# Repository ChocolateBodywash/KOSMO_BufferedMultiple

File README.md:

## KOSMO Format Buffered Multiple

A KOSMO format of a dead simple Buffered Multiple circuit. This one is 25cm, perfect for smaller setups

---
Note: This was created by a hobbyist with no formal engineering training outside various late night YouTube binges. 
I’ve confirmed these designs to work but I make no guarantees on the design working efficiently.. or working at all.

Additional credit: Analog Output (Richard Holmes) for footprint libraries and front panel templates.

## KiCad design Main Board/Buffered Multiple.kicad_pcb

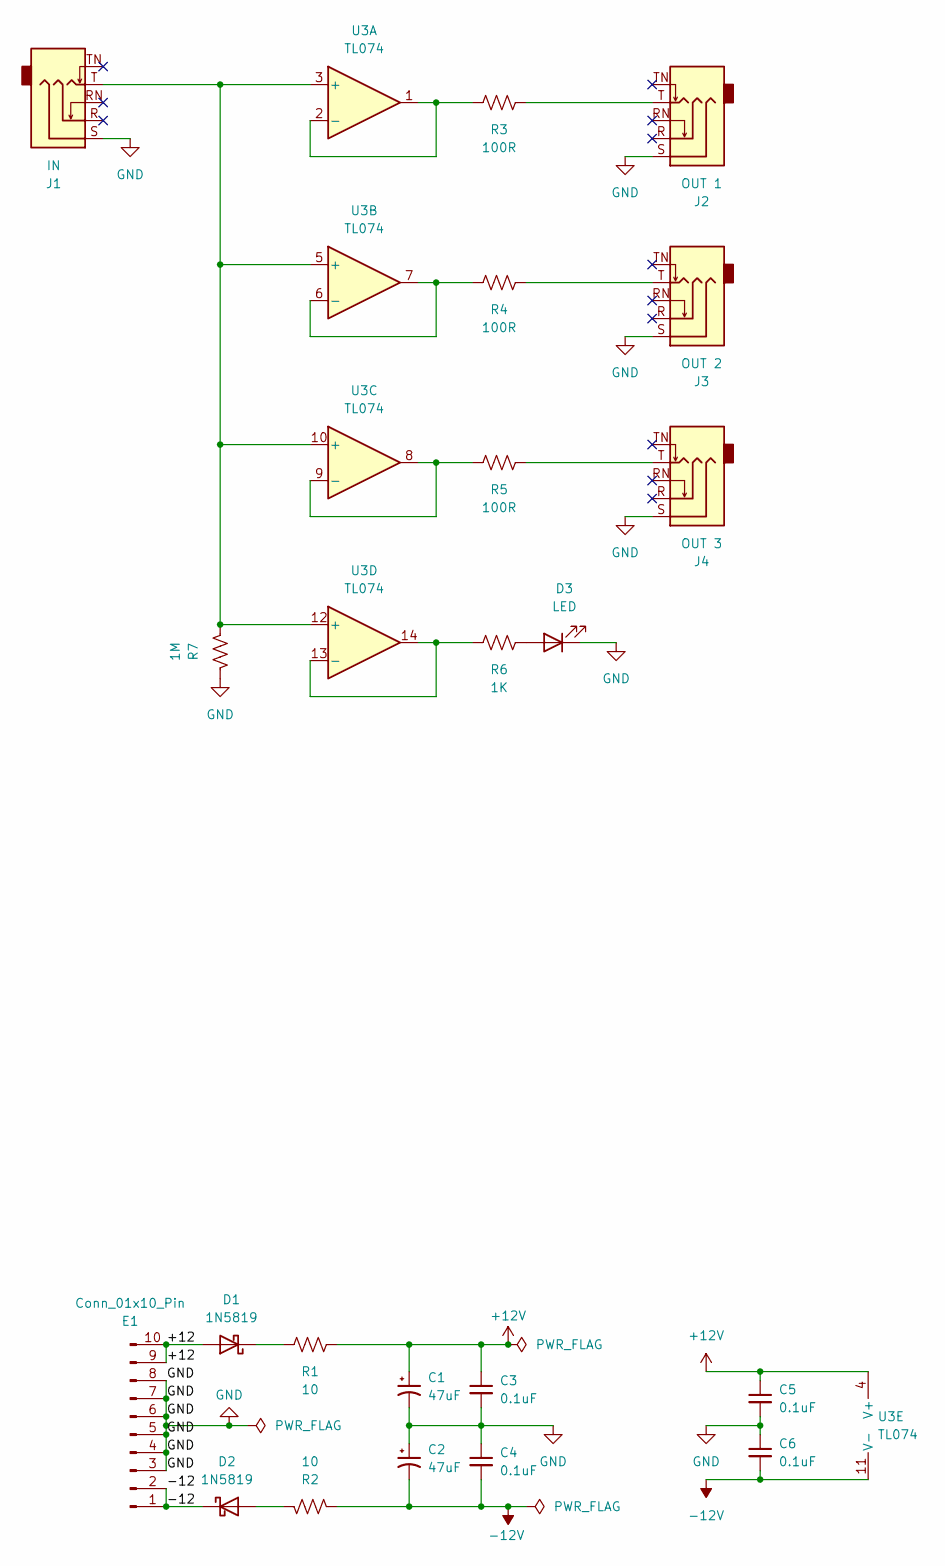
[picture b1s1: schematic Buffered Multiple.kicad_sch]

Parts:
C1, C2: 47uF; CP_Radial_D5.0mm_P2.50mm
C3, C4, C5, C6: 0.1uF; C_Disc_D3.0mm_W1.6mm_P2.50mm
D1, D2: 1N5819; D_DO-41_SOD81_P10.16mm_Horizontal
D3: LED; LED_D5.0mm
E1: Conn_01x10_Pin; Pins_2x05_2.54mm_TH_EurorackPower_Shrouded
J1: IN; Jack_6.35mm_PJ_629HAN
J2: OUT 1; Jack_6.35mm_PJ_629HAN
J3: OUT 2; Jack_6.35mm_PJ_629HAN
J4: OUT 3; Jack_6.35mm_PJ_629HAN
R1, R2: 10; R_Axial_DIN0207_L6.3mm_D2.5mm_P10.16mm_Horizontal
R3, R4, R5: 100R; R_Axial_DIN0207_L6.3mm_D2.5mm_P10.16mm_Horizontal
R6: 1K; R_Axial_DIN0207_L6.3mm_D2.5mm_P10.16mm_Horizontal
R7: 1M; R_Axial_DIN0207_L6.3mm_D2.5mm_P10.16mm_Horizontal
U3: TL074; DIP-14_W7.62mm

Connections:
+12V: C1.1, C3.1, C5.1, R1.2, U3.4 (V+)
-12V: C2.2, C4.2, C6.2, R2.2, U3.11 (V-)
/+12: D1.2 (A), E1.9, E1.10
/-12: D2.1 (K), E1.1, E1.2
GND: C1.2, C2.1, C3.2, C4.1, C5.2, C6.1, D3.1 (K), E1.3, E1.4, E1.5, E1.6, E1.7, E1.8, J1.S, J2.S, J3.S, J4.S, R7.1
unnamed: D1.1 (K), R1.1
unnamed: D2.2 (A), R2.1
unnamed: D3.2 (A), R6.2
unnamed: J2.T, R3.2
unnamed: J3.T, R4.2
unnamed: J4.T, R5.2
unnamed: J1.T, R7.2, U3.3 (+), U3.5 (+), U3.10 (+), U3.12 (+)
unnamed: R3.1, U3.1, U3.2 (-)
unnamed: R4.1, U3.6 (-), U3.7
unnamed: R5.1, U3.8, U3.9 (-)
unnamed: R6.1, U3.13 (-), U3.14

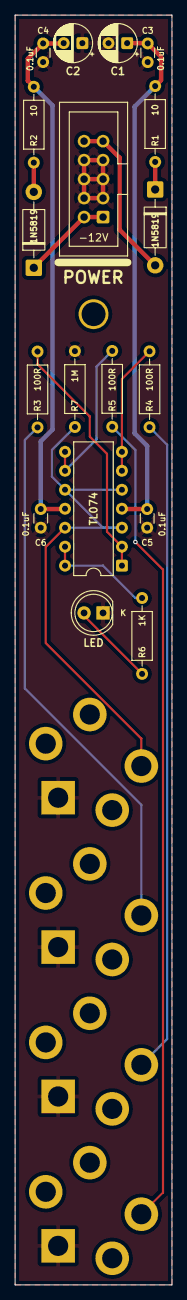
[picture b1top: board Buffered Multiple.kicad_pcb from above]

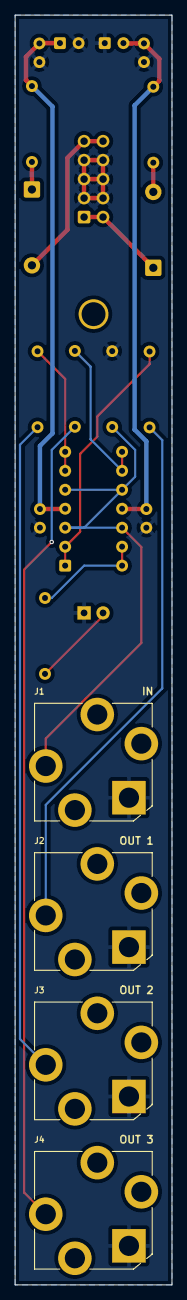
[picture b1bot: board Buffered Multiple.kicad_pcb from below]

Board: 2 copper layers, 21.0 x 170.0 mm, 23 parts (4 on the bottom side), 16 nets.

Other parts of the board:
M: Kosmo_Panel_Mounting_Hole

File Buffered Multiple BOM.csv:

Reference,Value,Datasheet,Package,Qty
"C1,C2",47uF,~,Electrolytic Capacitor,2
"C3,C4,C5,C6",0.1uF,~,Ceramic Disc Capacitor,4
"D1,D2",1N5819,http://www.vishay.com/docs/88525/1n5817.pdf,Diode_THT:D_DO-41_SOD81_P10.16mm_Horizontal,2
D3,LED,~,LED 5.0mm,1
E1,Conn_02x05_Pin,~,Pins_2x05_2.54mm_TH_EurorackPower_Shrouded,1
J1,IN,~,Jack_6.35mm,1
J2,OUT 1,~,Jack_6.35mm,1
J3,OUT 2,~,Jack_6.35mm,1
J4,OUT 3,~,Jack_6.35mm,1
"R1,R2",10,~,Metal Film 1/4 Resistor,2
"R3,R4,R5",100R,~,Metal Film 1/4 Resistor,3
R6,1K,~,Metal Film 1/4 Resistor,1
R7,1M,~,Metal Film 1/4 Resistor,1
U3,TL074,http://www.ti.com/lit/ds/symlink/tl071.pdf,Package_DIP:DIP-14_W7.62mm,1

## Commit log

2025-10-24 Upload Files
2025-10-27 Update image
2025-10-29 Upload Schematics
